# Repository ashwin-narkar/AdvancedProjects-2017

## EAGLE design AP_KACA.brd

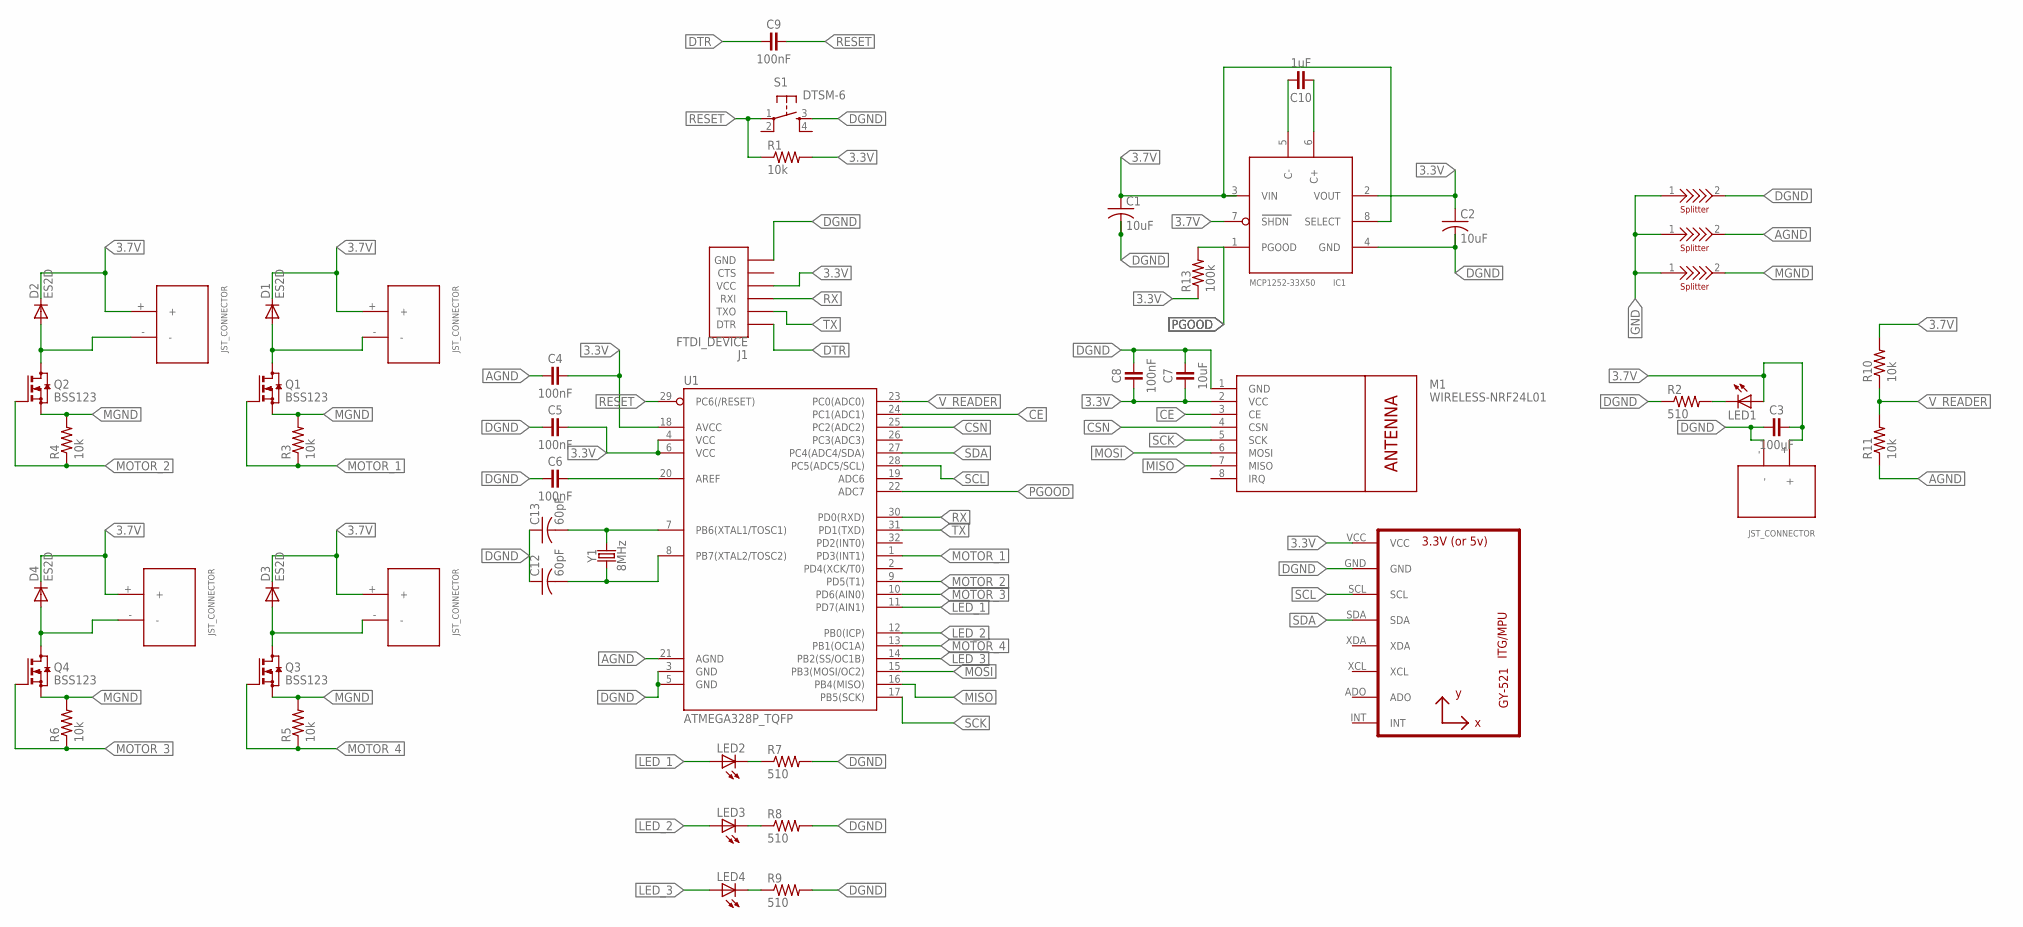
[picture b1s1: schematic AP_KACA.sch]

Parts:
C1, C2: 10uF; C1206
C3: 100uF; C1206
C4, C5, C6, C8, C9: 100nF; C0603
C7: 10uF; C0603
C10: 1uF; C0603
C12, C13: 60pF; RCL_C1206
D1, D2, D3, D4: ES2D; SMB
IC1: MCP1252-33X50; MSOP8
J1: FTDI_DEVICE; FTDI_DEVICE_SIDE
JST_MOTOR_1: JST_MOTOR_1; JST_CONNECTOR_FEMALE
LED1, LED2, LED3, LED4: LED_ESML0603; LED_SML0603
M1: WIRELESS-NRF24L01
Q1, Q2, Q3, Q4: BSS123; SOT23
R1, R3, R4, R5, R6, R10, R11: 10k; 0603
R2, R7, R8, R9: 510; 0603
R13: 100k; 0603
S1: DTSM-6
U1: ATMEGA328P_TQFP; TQFP32-08
U3: GY-521MPU6050; GY-521
U$2, U$3, U$4, U$5: JST_CONNECTOR_FEMALE
U$6, U$7, U$8: SPLITTER
Y1: 8MHz; HC49UP

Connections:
3.3V: C2.1, C4.2, C5.2, C7.1, C8.1, IC1.2 (VOUT), J1.P$4 (VCC), M1.2 (VCC), R1.2, R13.1, U1.4 (VCC), U1.6 (VCC), U1.18 (AVCC), U3.VCC
3.7V: C1.1, C3.2, D1.C, D2.C, D3.C, D4.C, IC1.3 (VIN), IC1.7 (SHDN), IC1.8 (SELECT), JST_MOTOR_1.+, LED1.A, R10.2, U$2.+, U$3.+, U$4.+, U$5.+
AGND: C4.1, R11.1, U1.21 (AGND), U$6.2
CE: M1.3 (CE), U1.24 (PC1(ADC1))
CSN: M1.4 (CSN), U1.25 (PC2(ADC2))
DGND: C1.2, C2.2, C3.1, C5.1, C6.1, C7.2, C8.2, C12.1, C13.1, IC1.4 (GND), J1.P$6 (GND), M1.1 (GND), R2.1, R7.2, R8.2, R9.2, S1.3, U1.3 (GND), U1.5 (GND), U3.GND, U$2.-, U$8.2
DTR: C9.1, J1.P$1 (DTR)
GND: U$6.1, U$7.1, U$8.1
LED_1: LED2.A, U1.11 (PD7(AIN1))
LED_2: LED3.A, U1.12 (PB0(ICP))
LED_3: LED4.A, U1.14 (PB2(SS/OC1B))
MGND: Q1.2 (S), Q2.2 (S), Q3.2 (S), Q4.2 (S), R3.2, R4.2, R5.2, R6.2, U$7.2
MISO: M1.7 (MISO), U1.16 (PB4(MISO))
MOSI: M1.6 (MOSI), U1.15 (PB3(MOSI/OC2))
MOTOR_1: Q1.1 (G), R3.1, U1.1 (PD3(INT1))
MOTOR_2: Q2.1 (G), R4.1, U1.9 (PD5(T1))
MOTOR_3: Q4.1 (G), R6.1, U1.10 (PD6(AIN0))
MOTOR_4: Q3.1 (G), R5.1, U1.13 (PB1(OC1A))
unnamed: D2.A, Q2.3 (D), U$3.-
unnamed: D1.A, JST_MOTOR_1.-, Q1.3 (D)
unnamed: D3.A, Q3.3 (D), U$5.-
unnamed: D4.A, Q4.3 (D), U$4.-
unnamed: LED1.C, R2.2
unnamed: C13.2, U1.7 (PB6(XTAL1/TOSC1)), Y1.2
unnamed: C12.2, U1.8 (PB7(XTAL2/TOSC2)), Y1.1
unnamed: C6.2, U1.20 (AREF)
unnamed: C10.2, IC1.5 (C-)
unnamed: C10.1, IC1.6 (C+)
unnamed: LED3.C, R8.1
unnamed: LED2.C, R7.1
unnamed: LED4.C, R9.1
PGOOD: IC1.1 (PGOOD), R13.2, U1.22 (ADC7)
RESET: C9.2, R1.1, S1.1, U1.29 (PC6(/RESET))
RX: J1.P$3 (RXI), U1.30 (PD0(RXD))
SCK: M1.5 (SCK), U1.17 (PB5(SCK))
SCL: U1.28 (PC5(ADC5/SCL)), U3.SCL
SDA: U1.27 (PC4(ADC4/SDA)), U3.SDA
TX: J1.P$2 (TXO), U1.31 (PD1(TXD))
V_READER: R10.1, R11.2, U1.23 (PC0(ADC0))

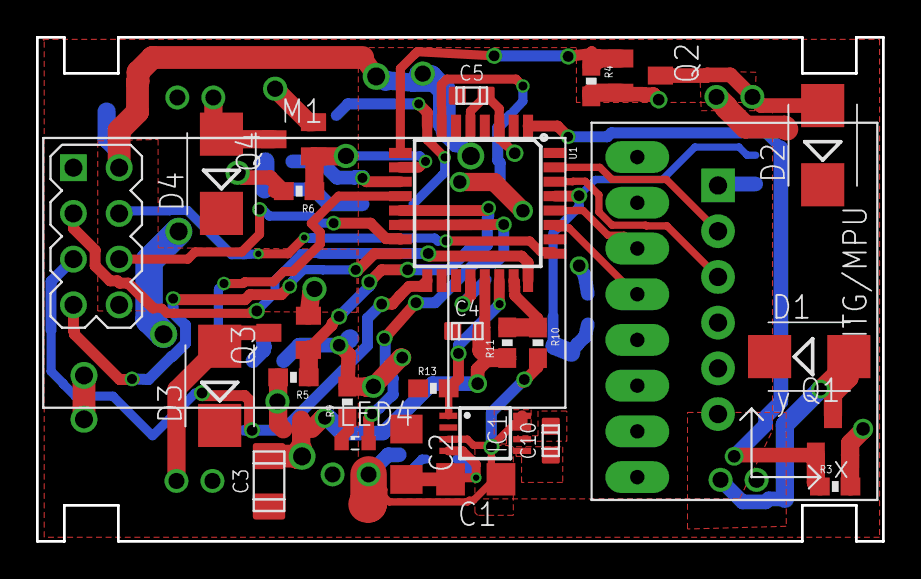
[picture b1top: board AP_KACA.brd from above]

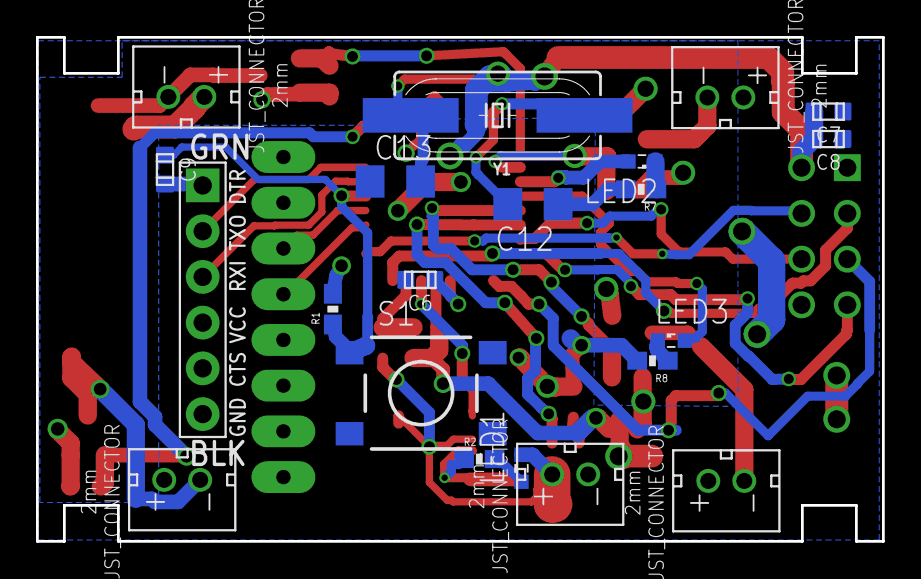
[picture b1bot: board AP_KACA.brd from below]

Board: 2 copper layers, 47.0 x 28.0 mm, 51 parts (21 on the bottom side), 39 nets.

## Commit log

2017-10-29 CPP File
2017-10-29 updated to add some change register functions
    AutoAck, setPALevel, setRetries
2017-10-29 Added rest of the files
    nRF24L01.h - added mappings for register defines
2017-10-29 added mappings for defines
2017-10-29 updated functions
2017-10-29 added Transmitter code for Arduino
2017-10-29 Added Teensy Receiver Code
    Testing to send one character from the Arduino to the Teensy
2017-10-29 changed setCRCLength
    updated setCRCLength
2017-10-29 Added Serial.begin in setup
2017-10-29 Fixed RF24 and Teensy code Bugs
2017-10-29 fixed setRetries and setAutoAck
    fixed bugs in those functions
2017-10-30 Fixed Bugs in write_register function
2017-10-30 Fixed write_register bugs again
2017-10-30 update rf24 read and write
    update read and write functions
2017-10-30 Updated Teensy Code
2017-10-30 testing arduino
    put blinking blue led in
2017-10-30 make sure on the right processor
    3.3V 8 MHz
2017-11-04 Fixed Teensy RF test and added final teensy code to begin
2017-11-04 started work on final teensy code
2017-11-05 Create arduinoFunctions
2017-11-05 Working sample of writing on arduino with RF24
2017-11-05 Added Final Arduino Code
2017-11-05 Finalized Teensy Code
    Fully Functional
2017-11-08 Begin Lab2
2017-11-08 Implemented readReg function
2017-11-17 sensor fusion arduino code
    read and write registers, tried changing the registers
2017-11-17 made some changes to sensor fusion
    some changes
2017-11-17 Fixed read reg function
2017-11-17 read register function
2017-11-17 finally fixed read and write register
2017-11-17 Added Vectors for Accel and Gyro
2017-11-17 Fixed sensor_fusion bug
2017-11-17 updated vector to work with library
2017-11-21 Finalized Code
2017-12-04 Started Lab3
2018-01-26 quadcopter schematic
    Started schematic for quadcopter
2018-01-26 Added some passives
    added some capacitors and resistors
2018-01-28 kind of finished quadcopter schematic
    added indicatory leds, voltage divider, pull down resistors for motors
2018-01-29 Added Controller Schematic
2018-01-29 added missing components
    there were some missing labels and parts of the schematic
2018-01-30 removed something
    removed the other imu
2018-01-30 fixed schematic according to design review notes
2018-01-31 Updated schematic
2018-02-02 not sure what was updated
    github says theres uncommitted changes
2018-02-08 Update SCH
2018-02-09 started board
    started pcb layout
2018-02-09 Almost done with board
    this is hard
2018-02-09 Airwires gone
2018-02-09 finished first draft of board
    got rid of all the drc errors
2018-02-14 started new pcb design ver 2
    ver 2 of quadcopter pcb
2018-02-14 did more traces
    just a few airwires left but they are hard to trace
2018-02-15 fixed airwires
    only 5 airwires left
2018-02-15 ALMOST completed pcb
    still needs the airwires for the splitter. fixed bottlenecks
2018-02-15 fixed dimensions
    one the board dimensions was off
2018-02-16 renamed files
    renamed files and one airwire left
2018-02-16 connected all the airwires
2018-02-16 Fixed Clearance Issue
    Yay
2018-02-16 version 3 board design
    component placement done

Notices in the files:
parts and their libraries:
SparkFun-Resistors: Licensing: Creative Commons ShareAlike 4.0 International - https://creativecommons.org/licenses/by-sa/4.0
